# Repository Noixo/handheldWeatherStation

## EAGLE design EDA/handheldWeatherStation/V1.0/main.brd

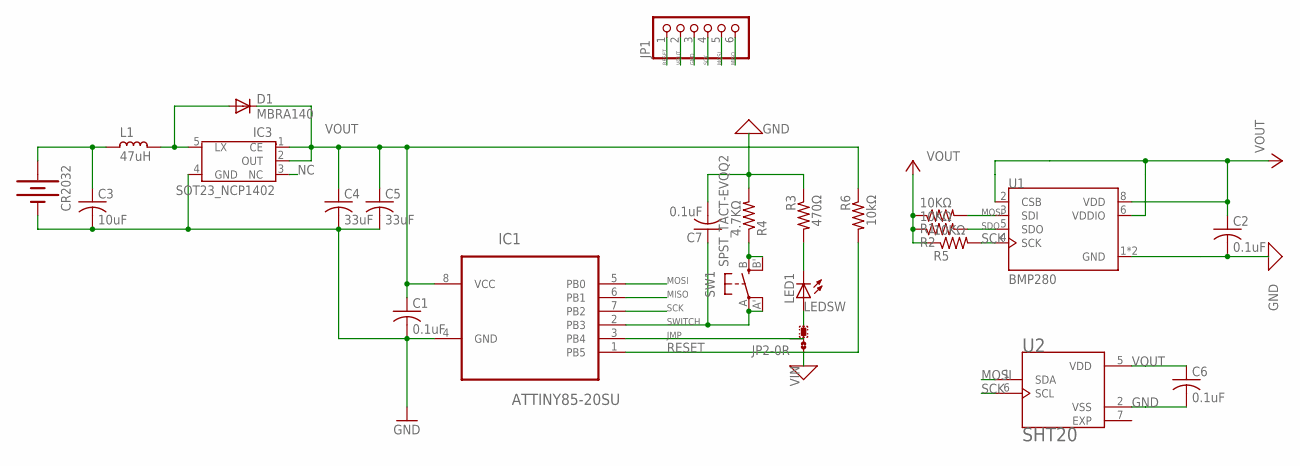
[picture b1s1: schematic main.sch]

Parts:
C1, C2, C6, C7: 0.1uF; C0805
C3: 10uF; C0805
C4, C5: 33uF; C1210
CR2032: BATTERY-20MM_SMD_4LEGS; BATTCON_20MM_4LEGS
D1: MBRA140; DO-214AC
IC1: ATTINY85-20SU; SOIC127P798X216-8N
IC3: SOT23_NCP1402; SOT-23-5
JP1: PINHD-1X6; 1X06
JP2: 0R-JUMPA; A0R-JMP
L1: 47uH; L0805
LED1: LEDCHIPLED_0603; CHIPLED_0603
R1, R2, R5: 10KΩ; R0805
R3: 470Ω; R0805
R4: 4.7KΩ; R0805
R6: 10kΩ; R0805
SW1: SPST_TACT-EVQQ2; EVQ-Q2
U1: BMP280; XDCR_BMP280
U2: SHT20; DFN300X300X110-7N

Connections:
GND: C1.2, C2.2, C3.2, C4.2, C5.2, C6.2, C7.2, CR2032.NEGATIVE (-), IC1.4 (GND), IC3.4 (GND), JP1.3, R3.1, R4.2, U1.1 (GND), U1.7 (GND), U2.2 (VSS)
JMP: IC1.3 (PB4), JP2.2
LEDRES: LED1.C, R3.2
LEDSW: JP2.3, LED1.A
LX: D1.A, IC3.5 (LX), L1.1
MISO: IC1.6 (PB1), JP1.6
MOSI: IC1.5 (PB0), JP1.5, R1.2, U1.3 (SDI), U2.1 (SDA)
NC: IC3.3 (NC)
RESET: IC1.1 (PB5), JP1.1, R6.2
SCK: IC1.7 (PB2), JP1.4, R5.2, U1.4 (SCK), U2.6 (SCL)
SDO: R2.2, U1.5 (SDO)
SWITCH: C7.1, IC1.2 (PB3), SW1.A, SW1.A' (P1)
SWITCHRES: R4.1, SW1.B (S), SW1.B' (S1)
VIN: C3.1, CR2032.POSITIVE@1 (+), CR2032.POSITIVE@2 (+), CR2032.POSITIVE@3 (+), CR2032.POSITIVE@4 (+), JP2.1, L1.2
VOUT: C1.1, C2.1, C4.1, C5.1, C6.1, D1.C, IC1.8 (VCC), IC3.1 (CE), IC3.2 (OUT), JP1.2, R1.1, R2.1, R5.1, R6.1, U1.2 (CSB), U1.6 (VDDIO), U1.8 (VDD), U2.5 (VDD)

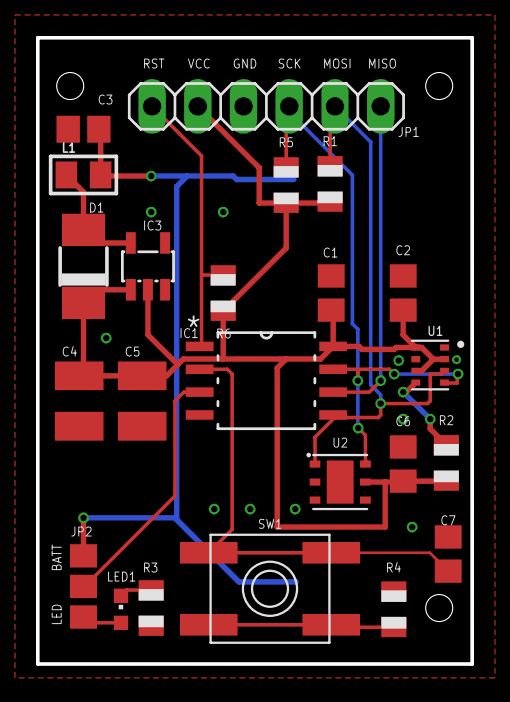
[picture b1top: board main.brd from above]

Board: 2 copper layers, 24.1 x 34.8 mm, 24 parts (1 on the bottom side), 14 nets.

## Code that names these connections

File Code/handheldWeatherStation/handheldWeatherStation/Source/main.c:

/*
 * handheldWeatherStation.c
 *
 * Created: 19/02/2018 00:16:46
 * Author : Matt
 */ 

/*
PB0: MOSI
PB1: MISO
PB2: SCK
PB3: button
PB4: led/batt
PB5: RST
*/

/*
current usage: (not including boost)

Display full: 4.6mA-5mA approx
Display dim: 3mA
Display sleep: 1.3mA - 1.5mA approx
Micro sleep + display off + no data: 0.0075mA
*/

#include <avr/pgmspace.h>
#include <util/delay.h>
#include <avr/eeprom.h>

#include "i2c.h"
#include "bmp280.h"
#include "oled.h"
#include "sht20.h"
#include "powerSave.h"
#include "display.h"

char microWake = 0xFF;

const uint8_t ssd1306_init_sequence [] PROGMEM = {	// Initialization Sequence
	0xAE,			// Display OFF (sleep mode)
	0x20, 0b00,		// Set Memory Addressing Mode
	// 00=Horizontal Addressing Mode; 01=Vertical Addressing Mode;
	// 10=Page Addressing Mode (RESET); 11=Invalid
	0xB0,			// Set Page Start Address for Page Addressing Mode, 0-7
	0xC8,			// Set COM Output Scan Direction
	0x00,			// ---set low column address
	0x10,			// ---set high column address
	0x40,			// --set start line address
	0x81, 0x3F,		// Set contrast control register
	0xA1,			// Set Segment Re-map. A0=address mapped; A1=address 127 mapped.
	0xA6,			// Set display mode. A6=Normal; A7=Inverse
	0xA8, 0x3F,		// Set multiplex ratio(1 to 64)
	0xA4,			// Output RAM to Display
	// 0xA4=Output follows RAM content; 0xA5,Output ignores RAM content
	0xD3, 0x00,		// Set display offset. 00 = no offset
	0xD5,			// --set display clock divide ratio/oscillator frequency
	0xF0,			// --set divide ratio
	0xD9, 0x22,		// Set pre-charge period
	0xDA, 0x12,		// Set com pins hardware configuration
	0xDB,			// --set vcomh
	0x20,			// 0x20,0.77xVcc
	0x8D, 0x14,		// Set DC-DC enable
	0xAF			// Display ON in normal mode
};

void butt_press()
{	
	if((PINB & (1 << PB3)) || microWake)	//read pin state. If HIGH then button NOT pressed & stop sending screen off cmd
	{
		oled_control(0xAE);	//turn off display
		microWake = 0;
	}
	//turn on display
	else
	{
		onWake();	//wake up peripherals 
		
		oled_control(0xAF);	//Turn on display
		
		//check battery level
		battery();

		//generate and display data
		display();
		
		//send off cmd if button not pushed (dumb ik)
		if(PINB & (1 << PB3))
			microWake = 0xFF;
	}
}

int main(void)
{
	PORTB = (0xFF);	//turn on all pullups
	_delay_ms(400);	//delay to let voltage stabilise
	
	adc_init();
	init_i2c();
	
	//start up OLED
	for (uint8_t i = 0; i < sizeof (ssd1306_init_sequence); i++) {
		oled_control(pgm_read_byte(&ssd1306_init_sequence[i]));
	}
	
	if(eeprom_read_byte((uint8_t*)0x00) == 0xFF)	//if new ATTINY
	{
		bmpCalibration();	//run calibration to save data in EEPROM
		eeprom_write_byte(0, 0);
	}

	bmpReset();
	
	//change contrast to brightest
	oled_control(0x81);
	oled_control(0xFF);
	
	//clear oled of random data
	oled_clear();
	
    while(1)
    {
		butt_press();

		//deep sleep for 1 sec
		sleep();
    }
	return 0;
}

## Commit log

2018-10-14 bmp280 data displaying
2018-10-15 added sht20 code
2018-10-16 fixed bug with bmp280, ADC working
2018-10-16 add file to git
2018-11-07 Added power saving
2019-01-05 Added gitignore
2019-01-05 removed redundant files?
2019-01-05 Separated files into subfolder
2019-01-14 Cleaned main.c, release 1.0
2019-01-18 Added schematics & enclosure
2019-01-18 Reuploaded code
2019-01-19 improved power saving

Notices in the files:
parts and their libraries:
SparkFun-Batteries: Licensing: Creative Commons ShareAlike 4.0 International - https://creativecommons.org/licenses/by-sa/4.0
rc-master: Copyright (C) 2007, Bob Starr
